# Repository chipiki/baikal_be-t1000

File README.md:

# baikal_be-t1000

## English

OpenHardware development board for Russian Baikal BE-T1000 MIPS Warrior P-class P5600 processor

Project status is "active schematic development". So, we haven't production PCB at this moment.

#### How to get this project:

First of all, get KiCAD EDA at http://kicad-pcb.org/download/

Install Git at https://git-scm.com/downloads if you don't have it allready.

Then do this commands in git-bash:
1) git clone https://github.com/chipiki/baikal_be-t1000.git
2) cd baikal_be-t1000
3) git submodule init
4) git submodule update
5) git submodule sync

Then launch KiCAD and open project file "baikal_be-t100.pro". 

## Русский

Открытый проект отладочной платы для отечественного процессора Байкал BE-T1000 MIPS32 Warrior P-class P5600.

Проект в стадии активной разработки схемы. Так, что, пока, готовой версии печатной платы нет на данный момент.

#### Как получить проект:

Для начала нужно скачать KiCAD на http://kicad-pcb.org/download/

Потом, необходимо установить Git отсюда https://git-scm.com/downloads , если он ещё не был установлен ранее.

Затем необходимо выполнить следующие команды в git-bash:
1) git clone https://github.com/chipiki/baikal_be-t1000.git
2) cd baikal_be-t1000
3) git submodule init
4) git submodule update
5) git submodule sync

Затем запустите KiCAD и откройте файл проекта "baikal_be-t100.pro".

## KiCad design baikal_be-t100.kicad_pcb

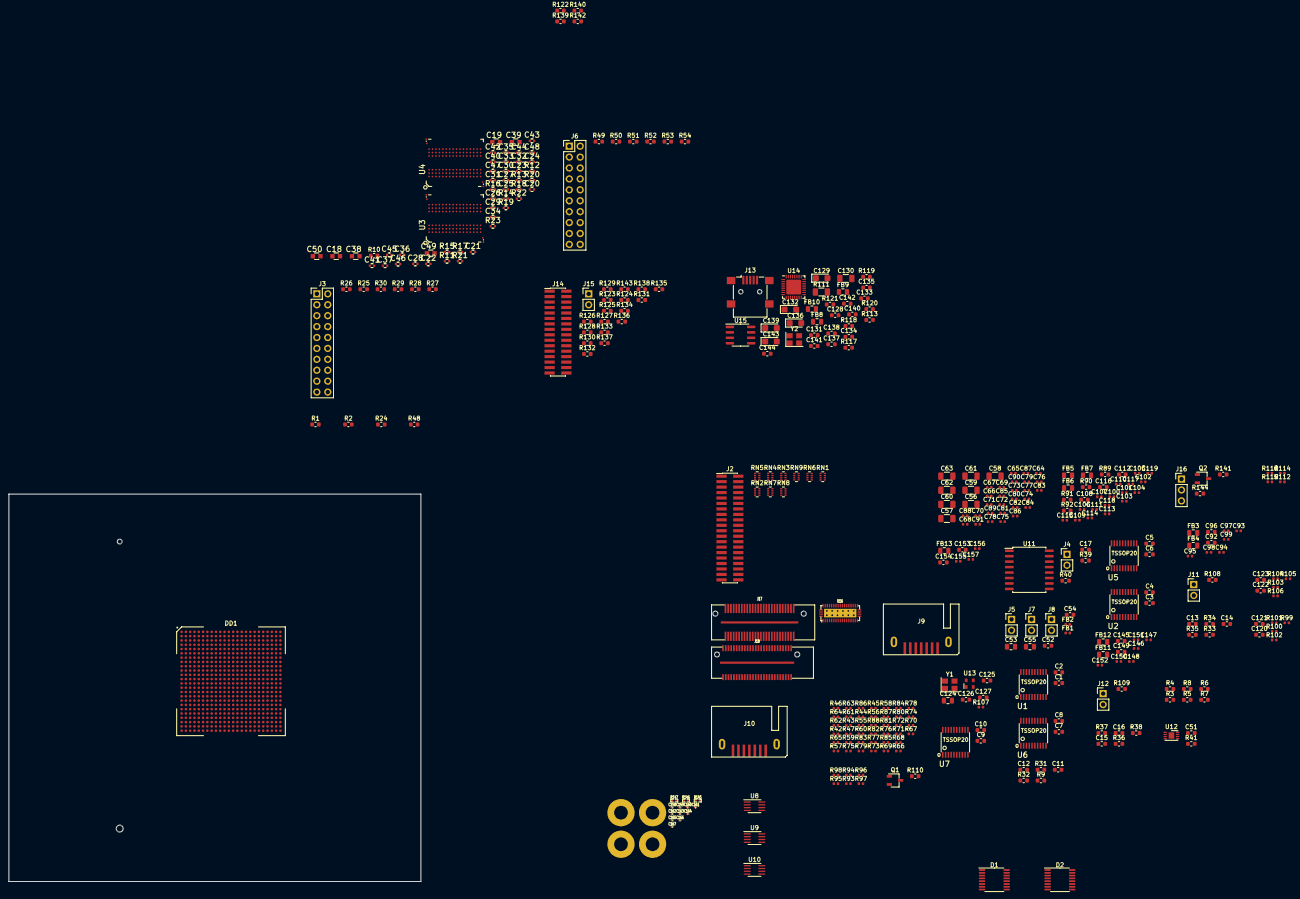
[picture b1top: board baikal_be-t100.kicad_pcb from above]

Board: 4 copper layers, 95.9 x 90.2 mm, 381 parts (1 on the bottom side), 402 nets, no tracks yet.

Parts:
C1, C2, C3, C4, C5, C6, C7, C8, C9, C10, C11, C12, C13, C14, C15, C16, C17, C51, C52, C54, C128, C131, C135, C137, C140, C142, C144: 0.1uF; C_0603_1608Metric
C18, C38, C39, C49, C50: 10uF/6.3V/20%; C_0603_5MIL_DWS
C19: 1uF/10V/10%; C_0603_5MIL_DWS
C20, C21, C22, C23, C24, C25, C26, C27, C28, C29, C30, C31, C32, C33, C34, C35, C36, C37, C40, C41, C42, C43, C44, C45, C46, C47, C48: 100nF/10V/10%; C_0402_5MIL_DWS
C53: 22uF; C_0805_2012Metric
C55, C124: 1uF; C_0805_2012Metric
C56, C57, C58, C59, C60, C61, C62, C63: 100uF; C_1206_3216Metric
C64, C65, C66, C67: 4.7uF; C_0402_1005Metric
C68, C69, C70, C71: 1uF; C_0402_1005Metric
C72, C73, C74, C75: 0.22uF; C_0402_1005Metric
C76, C77, C78, C79, C80, C81, C82, C83: 0.1uF; C_0402_1005Metric
C84, C85, C86, C87: 0.047uF; C_0402_1005Metric
C88, C89, C90, C91: 0.022uF; C_0402_1005Metric
C92, C96, C108, C112, C116, C145, C149, C153: 10uF/6.3V/0603; C_0603_1608Metric
C93, C97, C109, C113, C117, C146, C150: 4.7uF/10V/0402; C_0402_1005Metric
C94, C98, C110, C114, C118, C147, C151, C155: 0.1uF/10V/0402; C_0402_1005Metric
C95, C99, C111, C115, C119, C148, C152, C156, C157: 0.01uF/10V/0402; C_0402_1005Metric
C100, C101, C102, C103, C104, C105, C106, C107: 0.01uF; C_0402_1005Metric
C120, C121, C122, C123: 0.1uF/16V/X7R; C_0603_1608Metric
C125, C138, C141: 0.01uF; C_0603_1608Metric
C126, C127: 12pF; C_0603_1608Metric
C129, C132: 4.7uF/6.3V; CP_EIA-3216-18_Kemet-A
C130: 0.1uF; C_1206_3216Metric
C133, C134: 33pF; C_0603_1608Metric
C136, C139, C143: 10uF/6.3V; CP_EIA-3216-18_Kemet-A
C154: 1uF/10V/0402; C_0603_1608Metric
C158, C159, C163, C164, C165: 10nF; c_0201
C160, C161, C162, C166, C167: 100nF; c_0201
D1, D2: SN74AVC4T774PWR; TSSOP-16_4.4x5mm_P0.65mm
DD1: Baikal_BE-T1000; BGA-576_24x24_25.0x25.0mm
FB1, FB2: BLM15AX601SN1D; L_0402_1005Metric
FB3, FB4, FB5, FB6, FB7, FB11, FB12, FB13: MPZ2012S101AT000; L_0805_2012Metric
FB8, FB9, FB10: 500mA / 0.1DCR; L_0805_2012Metric
H1, H2, H3, H4: PCB_HOLE; PCIE104_HOLE
J1: 2-2013289-1; TE_2-2013289-1
J2: Conn_02x20_Odd_Even; PinHeader_2x20_P1.27mm_Vertical_SMD
J3, J6: Conn_02x10_Odd_Even; PinHeader_2x10_P2.54mm_Vertical
J4, J5, J7, J8, J11, J12, J15: Conn_01x02; PinHeader_1x02_P2.54mm_Vertical
J9, J10: 0473065005; SATA-MALE-7
J13: USB_OTG; USB_Mini-B_Lumberg_2486_01_Horizontal
J14: Conn_02x16_Odd_Even; PinHeader_2x16_P1.27mm_Vertical_SMD
J16: Conn_01x03; PinHeader_1x03_P2.54mm_Vertical
J17: OneBank Bottom; ASP-129646-22
J18: OneBank Top; ASP-129637-13
Q1, Q2: FDV305N; TSOT-23
R1, R10: 240; R_0603_1608Metric
R2: 200; R_0603_1608Metric
R3, R4, R5, R6, R7, R8, R9, R31, R32, R33, R34, R35, R36, R37, R38, R39, R40: 3K3; R_0603_1608Metric
R11, R12: 22R; R_0402_5MIL_DWS
R13, R14, R15, R16, R19: 2k/1%; R_0402_5MIL_DWS
R17, R22: 243R/1%; R_0402_5MIL_DWS
R18, R23: NA(243R/1%); R_0402_5MIL_DWS
R20: 100R/1%; R_0402_5MIL_DWS
R21: NA; R_0402_5MIL_DWS
R24, R48, R122, R123, R124, R125, R126, R127, R128, R129, R130, R131, R132, R133, R134, R135, R136, R137, R138, R139, R140: 33; R_0603_1608Metric
R25, R26, R27, R28, R29, R30, R49, R50, R51, R52, R53, R54: 47K; R_0603_1608Metric
R41: 0R; R_0603_1608Metric
R42, R43, R44, R45, R55, R56, R57, R58, R99, R100, R101, R102, R103, R104, R105, R106: 10K; R_0402_1005Metric
R46, R47, R59, R60: 4K7; R_0402_1005Metric
R61, R62, R63, R64, R65, R66, R67, R68, R69, R70, R71, R72, R73, R74, R75, R76, R77, R78, R79, R80, R81, R82, R83, R84: 33R; R_0402_1005Metric
R85, R86, R87, R88: 1K; R_0402_1005Metric
R89, R90, R91, R92, R118, R119: 0; R_0603_1608Metric
R93, R94, R95, R96, R97, R98, R107, R112, R114, R115, R116: 22R; R_0402_1005Metric
R108, R109, R120, R121, R142, R143: 4K7; R_0603_1608Metric
R110, R141, R144: 10K; R_0603_1608Metric
R111: 1M; R_1206_3216Metric
R113: 1M; R_0603_1608Metric
R117: 12K; R_0603_1608Metric
R145: DNP; r_0402
R146, R147: 10K; r_0402
RN1, RN2, RN3, RN4, RN5, RN6, RN7, RN8, RN9: YC124-JR-07100KL; R_Array_Concave_4x0402
U1, U2, U5, U6, U7: TXB0108PWR(TSSOP-20); TSSOP20_Pitch-0.65mm_6.6x4.5x1.2mm
U3, U4: K4B4G1646Q-HYK0(FBGA-96_256Mx16_DDR3-1600_11-11-1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; FBGA96(HYNIX_SAMSUNG_512MX16_DDR3)
U8, U9, U10: TCA9406DC; SSOP-8_2.95x2.8mm_P0.65mm
U11: DS3231M; SOIC-16W_7.5x10.3mm_P1.27mm
U12: AT24CS04-MAHM; DFN-8-1EP_3x2mm_P0.5mm_EP1.3x1.5mm
U13: ASDMB-xxxMHz; Oscillator_SMD_Abracon_ASDMB-4Pin_2.5x2.0mm
U14: USB3300-EZK; QFN-32-1EP_5x5mm_P0.5mm_EP3.45x3.45mm
U15: MIC2025-1YM; SOIC-8_3.9x4.9mm_P1.27mm
U16: CBTL04083A; HVQFN42
Y1: KX-7T 25MHz; Crystal_SMD_3225-4Pin_3.2x2.5mm
Y2: 24MHz; Crystal_SMD_3225-4Pin_3.2x2.5mm

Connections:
+0V95: C56.1, C57.1, C58.1, C59.1, C60.1, C61.1, C62.1, C63.1, C64.1, C65.1, C66.1, C67.1, C68.1, C69.1, C70.1, C71.1, C72.1, C73.1, C74.1, C75.1, C76.1, C77.1, C78.1, C79.1, C80.1, C81.1, C82.1, C83.1, C84.1, C85.1, C86.1, C87.1, C88.1, C89.1, C90.1, C91.1, DD1.A1, DD1.A8, DD1.A15, DD1.A22, DD1.AB4, DD1.AC1, DD1.AC19, DD1.AC20, DD1.E1, DD1.E16, DD1.G8, DD1.G9, DD1.G10, DD1.G11, DD1.G12, DD1.G13, DD1.G14, DD1.G15, DD1.G16, DD1.G22, DD1.J8, DD1.J9, DD1.J10, DD1.J11, DD1.J12, DD1.J13, DD1.J14, DD1.J15, DD1.J16, DD1.L8, DD1.L9, DD1.L10, DD1.L11, DD1.L12, DD1.L13, DD1.L14, DD1.L15, DD1.L16, DD1.M1, DD1.N8, DD1.N9, DD1.N10, DD1.N11, DD1.N12, DD1.N13, DD1.N14, DD1.N15, DD1.N16, DD1.R8, DD1.R9, DD1.R10, DD1.R11, DD1.R12, DD1.R13, DD1.R14, DD1.R15, DD1.R16, DD1.R22, DD1.U8, DD1.U9, DD1.U10, DD1.U11, DD1.U12, DD1.U13, DD1.U14, DD1.U15, DD1.U16, DD1.V3, DD1.W22, FB3.2, FB5.2, FB6.2, FB11.2
+1.5V: C18.1, C19.1, C20.1, C21.1, C22.1, C23.1, C24.2, C27.1, C30.1, C31.1, C32.1, C33.1, C34.1, C35.1, C36.1, C37.1, C38.1, C39.1, C41.1, C42.1, C43.1, C44.1, C45.1, C46.1, C47.1, C48.1, C49.1, C50.1, R13.2, R15.2, R19.2, U3.A1, U3.A8, U3.B2, U3.C1, U3.C9, U3.D2, U3.D9, U3.E9, U3.F1, U3.G7, U3.H2, U3.H9, U3.K2, U3.K8, U3.N1, U3.N9, U3.R1, U3.R9, U4.A1, U4.A8, U4.B2, U4.C1, U4.C9, U4.D2, U4.D9, U4.E9, U4.F1, U4.G7, U4.H2, U4.H9, U4.K2, U4.K8, U4.N1, U4.N9, U4.R1, U4.R9
+1V5: DD1.AB22, DD1.C22, DD1.D20, DD1.F19, DD1.H19, DD1.J24, DD1.K21, DD1.L19, DD1.L24, DD1.N18, DD1.N21, DD1.N24, DD1.R20, DD1.U20, DD1.U23, DD1.Y20, FB4.2, FB12.2
+1V8: C1.1, C3.1, C5.1, C7.1, C9.1, C11.1, C13.1, C15.1, C51.1, C120.1, C122.1, C124.1, C125.1, D1.16, D2.16, DD1.AB3, DD1.C4, DD1.C6, DD1.C7, DD1.C10, DD1.C12, DD1.F3, DD1.H3, DD1.L3, DD1.P3, DD1.T3, DD1.W3, DD1.Y17, FB1.1, FB2.1, FB7.2, FB13.2, J3.1, J6.1, J11.1, J12.1, J15.1, Q2.3, R3.1, R4.1, R5.1, R6.1, R7.1, R8.1, R25.1, R26.1, R27.1, R28.1, R29.1, R30.1, R41.1, R42.1, R43.1, R44.1, R45.1, R46.1, R47.1, R49.1, R50.1, R51.1, R52.1, R53.1, R54.1, R55.1, R56.1, R57.1, R58.1, R59.1, R60.1, R99.2, R100.2, R101.2, R103.2, R104.2, R105.2, R110.2, R142.1, U1.2, U1.10, U2.2, U2.10, U5.2, U5.10, U6.2, U6.10, U7.2, U7.10, U8.3, U9.3, U10.3, U12.8, U13.4
+1V35: J1.85, J1.86, J1.93, J1.94, J1.101, J1.102, J1.109, J1.110, J1.115, J1.116, J1.123, J1.124, J1.131, J1.132
+3.3V: C160.2, C161.2, C162.2, U16.5, U16.8, U16.13, U16.18, U16.20, U16.30, U16.40, U16.42
+3V3: C2.2, C4.2, C6.2, C8.2, C10.2, C12.2, C14.2, C16.2, C17.1, C121.1, C123.1, D1.15, D2.15, FB9.1, FB10.1, J1.199, J2.1, R9.1, R31.1, R32.1, R33.1, R34.1, R35.1, R36.1, R37.1, R38.1, R39.1, R40.1, RN1.1, RN1.2, RN1.3, RN1.4, RN2.1, RN2.2, RN2.3, RN2.4, RN3.1, RN3.2, RN3.3, RN3.4, RN4.1, RN4.2, RN4.3, RN4.4, RN5.1, RN5.2, RN5.3, RN5.4, RN6.1, RN6.2, RN6.3, RN6.4, RN7.1, RN7.2, RN7.3, RN7.4, RN8.1, RN8.2, RN8.3, RN8.4, RN9.1, RN9.2, RN9.3, RN9.4, U1.19, U2.19, U5.19, U6.19, U7.19, U8.6, U8.7, U9.6, U9.7, U10.6, U10.7, U11.2
+5V: C135.1, J17.53, J18.53, R145.2, U15.7
/CPU/CPU_1G_Eth/ZZZZZ: R65.2, R67.2, R69.2, R71.2, R73.2, R75.2, R77.2, R79.2, R81.2, R83.2
/CPU/CPU_BOOT/BOOTCFG_0: DD1.AC3, J11.2, R108.1
/CPU/CPU_BOOT/BOOTCFG_1: DD1.AC4, J12.2, R109.1
/CPU/CPU_BOOT/CLK_25M_IN: C127.1, DD1.R2, Y1.3
/CPU/CPU_BOOT/CLK_25M_OUT: C126.1, DD1.R1, Y1.1
/CPU/CPU_BOOT/RESET: DD1.T1, Q1.3, R110.1
/CPU/CPU_DEBUG/CPU_EJTAG/EJTAG20_Conn/DBGRQ: DD1.A14, J3.17, R30.2
/CPU/CPU_DEBUG/CPU_EJTAG/EJTAG20_Conn/TCK: DD1.A13, J3.9, R28.2
/CPU/CPU_DEBUG/CPU_EJTAG/EJTAG20_Conn/TDI: DD1.C14, J3.5, R26.2
/CPU/CPU_DEBUG/CPU_EJTAG/EJTAG20_Conn/TDO: J3.13, R24.2, R29.2
/CPU/CPU_DEBUG/CPU_EJTAG/EJTAG20_Conn/TMS: DD1.B14, J3.7, R27.2
/CPU/CPU_DEBUG/CPU_EJTAG/EJTAG20_Conn/nTRST: DD1.B13, J3.3, R25.2
/CPU/CPU_DEBUG/CPU_JTAG/JTAG20_Conn/DBGRQ: J6.17, R54.2
/CPU/CPU_DEBUG/CPU_JTAG/JTAG20_Conn/TCK: DD1.AA1, J6.9, R52.2
/CPU/CPU_DEBUG/CPU_JTAG/JTAG20_Conn/TDI: DD1.AB2, J6.5, R50.2
/CPU/CPU_DEBUG/CPU_JTAG/JTAG20_Conn/TDO: DD1.AB1, J6.13, R53.2
/CPU/CPU_DEBUG/CPU_JTAG/JTAG20_Conn/TMS: DD1.AA2, J6.7, R51.2
/CPU/CPU_DEBUG/CPU_JTAG/JTAG20_Conn/nTRST: J6.3, R48.2, R49.2
/CPU/CPU_DEBUG/CPU_TRACE/TR_CLK: J14.15, R122.2
/CPU/CPU_DEBUG/CPU_TRACE/TR_DATA0: J14.2, R123.2
/CPU/CPU_DEBUG/CPU_TRACE/TR_DATA1: J14.4, R124.2
/CPU/CPU_DEBUG/CPU_TRACE/TR_DATA2: J14.6, R125.2
/CPU/CPU_DEBUG/CPU_TRACE/TR_DATA3: J14.8, R126.2
/CPU/CPU_DEBUG/CPU_TRACE/TR_DATA4: J14.10, R127.2
/CPU/CPU_DEBUG/CPU_TRACE/TR_DATA5: J14.12, R128.2
/CPU/CPU_DEBUG/CPU_TRACE/TR_DATA6: J14.14, R129.2
/CPU/CPU_DEBUG/CPU_TRACE/TR_DATA7: J14.16, R130.2
/CPU/CPU_DEBUG/CPU_TRACE/TR_DATA8: J14.18, R131.2
/CPU/CPU_DEBUG/CPU_TRACE/TR_DATA9: J14.20, R132.2
/CPU/CPU_DEBUG/CPU_TRACE/TR_DATA10: J14.22, R133.2
/CPU/CPU_DEBUG/CPU_TRACE/TR_DATA11: J14.24, R134.2
/CPU/CPU_DEBUG/CPU_TRACE/TR_DATA12: J14.26, R135.2
/CPU/CPU_DEBUG/CPU_TRACE/TR_DATA13: J14.28, R136.2
/CPU/CPU_DEBUG/CPU_TRACE/TR_DATA14: J14.30, R137.2
/CPU/CPU_DEBUG/CPU_TRACE/TR_DATA15: J14.32, R138.2
/CPU/CPU_DEBUG/CPU_TRACE/TR_DM: J14.17, R139.2
/CPU/CPU_DEBUG/CPU_TRACE/TR_PROBE_N: DD1.E13, J14.19, R142.2
/CPU/CPU_DEBUG/CPU_TRACE/TR_TEST: DD1.F14, J14.9, J15.2, R143.2
/CPU/CPU_DEBUG/CPU_TRACE/TR_TRIGIN: DD1.D13, J14.21
/CPU/CPU_DEBUG/CPU_TRACE/TR_TRIGOUT: J14.23, R140.2
/CPU/CPU_DEBUG/CPU_TRACE/TSTSEL_3: DD1.U3, J14.29, Q2.2, R144.2
/CPU/CPU_GPIO/GPIO3_0: DD1.W7, U7.1
/CPU/CPU_GPIO/GPIO3_0_3V3: J2.30, RN9.8, U7.20
/CPU/CPU_GPIO/GPIO3_1: DD1.W6, U7.3
/CPU/CPU_GPIO/GPIO3_1_3V3: J2.32, RN9.7, U7.18
/CPU/CPU_GPIO/GPIO3_2: DD1.W5, U7.4
/CPU/CPU_GPIO/GPIO3_2_3V3: J2.34, RN9.6, U7.17
/CPU/CPU_GPIO/GPIO_0: DD1.F9, U1.1
/CPU/CPU_GPIO/GPIO_0_3V3: J2.3, RN1.8, U1.20
/CPU/CPU_GPIO/GPIO_1: DD1.F8, U1.3
/CPU/CPU_GPIO/GPIO_1_3V3: J2.5, RN1.7, U1.18
/CPU/CPU_GPIO/GPIO_2: DD1.F7, U1.4
/CPU/CPU_GPIO/GPIO_2_3V3: J2.7, RN1.6, U1.17
/CPU/CPU_GPIO/GPIO_3: DD1.E6, U1.5
/CPU/CPU_GPIO/GPIO_3_3V3: J2.9, RN1.5, U1.16
/CPU/CPU_GPIO/GPIO_4: DD1.E5, U1.6
/CPU/CPU_GPIO/GPIO_4_3V3: J2.11, RN2.8, U1.15
/CPU/CPU_GPIO/GPIO_5: DD1.E4, U1.7
/CPU/CPU_GPIO/GPIO_5_3V3: J2.13, RN2.7, U1.14
/CPU/CPU_GPIO/GPIO_6: DD1.D5, U1.8
/CPU/CPU_GPIO/GPIO_6_3V3: J2.15, RN2.6, U1.13
/CPU/CPU_GPIO/GPIO_7: DD1.D3, U1.9
/CPU/CPU_GPIO/GPIO_7_3V3: J2.17, RN2.5, U1.12
/CPU/CPU_GPIO/GPIO_8: DD1.A5, U2.1
/CPU/CPU_GPIO/GPIO_8_3V3: J2.19, RN3.8, U2.20
/CPU/CPU_GPIO/GPIO_9: DD1.D2, U2.3
/CPU/CPU_GPIO/GPIO_9_3V3: J2.21, RN3.7, U2.18
/CPU/CPU_GPIO/GPIO_10: DD1.D1, U2.4
/CPU/CPU_GPIO/GPIO_10_3V3: J2.23, RN3.6, U2.17
/CPU/CPU_GPIO/GPIO_11: DD1.C5, U2.5
/CPU/CPU_GPIO/GPIO_11_3V3: J2.25, RN3.5, U2.16
/CPU/CPU_GPIO/GPIO_12: DD1.C3, U2.6
/CPU/CPU_GPIO/GPIO_12_3V3: J2.27, RN4.8, U2.15
/CPU/CPU_GPIO/GPIO_13: DD1.C2, U2.7
/CPU/CPU_GPIO/GPIO_13_3V3: J2.29, RN4.7, U2.14
/CPU/CPU_GPIO/GPIO_14: DD1.B5, U2.8
/CPU/CPU_GPIO/GPIO_14_3V3: J2.31, RN4.6, U2.13
/CPU/CPU_GPIO/GPIO_15: DD1.B3, U2.9
/CPU/CPU_GPIO/GPIO_15_3V3: J2.33, RN4.5, U2.12
/CPU/CPU_GPIO/GPIO_16: DD1.E3, U5.1
/CPU/CPU_GPIO/GPIO_16_3V3: J2.35, RN5.8, U5.20
/CPU/CPU_GPIO/GPIO_17: DD1.B2, U5.3
/CPU/CPU_GPIO/GPIO_17_3V3: J2.37, RN5.7, U5.18
/CPU/CPU_GPIO/GPIO_18: DD1.C1, U5.4
/CPU/CPU_GPIO/GPIO_18_3V3: J2.39, RN5.6, U5.17
/CPU/CPU_GPIO/GPIO_19: DD1.A2, U5.5
/CPU/CPU_GPIO/GPIO_19_3V3: J2.4, RN5.5, U5.16
/CPU/CPU_GPIO/GPIO_20: DD1.A4, U5.6
/CPU/CPU_GPIO/GPIO_20_3V3: J2.6, RN6.8, U5.15
/CPU/CPU_GPIO/GPIO_21: DD1.B4, U5.7
/CPU/CPU_GPIO/GPIO_21_3V3: J2.8, RN6.7, U5.14
/CPU/CPU_GPIO/GPIO_22: DD1.A3, U5.8
/CPU/CPU_GPIO/GPIO_22_3V3: J2.10, RN6.6, U5.13
/CPU/CPU_GPIO/GPIO_23: DD1.B6, U5.9
/CPU/CPU_GPIO/GPIO_23_3V3: J2.12, RN6.5, U5.12
/CPU/CPU_GPIO/GPIO_24: DD1.A6, U6.1
/CPU/CPU_GPIO/GPIO_24_3V3: J2.14, RN7.8, U6.20
/CPU/CPU_GPIO/GPIO_25: DD1.F10, U6.3
/CPU/CPU_GPIO/GPIO_25_3V3: J2.16, RN7.7, U6.18
/CPU/CPU_GPIO/GPIO_26: DD1.E8, U6.4
/CPU/CPU_GPIO/GPIO_26_3V3: J2.18, RN7.6, U6.17
/CPU/CPU_GPIO/GPIO_27: DD1.E7, U6.5
/CPU/CPU_GPIO/GPIO_27_3V3: J2.20, RN7.5, U6.16
/CPU/CPU_GPIO/GPIO_28: DD1.B7, U6.6
/CPU/CPU_GPIO/GPIO_28_3V3: J2.22, RN8.8, U6.15
/CPU/CPU_GPIO/GPIO_29: DD1.A7, U6.7
/CPU/CPU_GPIO/GPIO_29_3V3: J2.24, RN8.7, U6.14
/CPU/CPU_GPIO/GPIO_30: DD1.E9, U6.8
/CPU/CPU_GPIO/GPIO_30_3V3: J2.26, RN8.6, U6.13
/CPU/CPU_GPIO/GPIO_31: DD1.D8, U6.9
/CPU/CPU_GPIO/GPIO_31_3V3: J2.28, RN8.5, U6.12
/CPU/CPU_I2C/I2C0_SCL: DD1.AD5, R3.2, U8.5
/CPU/CPU_I2C/I2C0_SCL_3V3: R9.2, U8.8
/CPU/CPU_I2C/I2C0_SDA: DD1.AD4, R4.2, U8.4
/CPU/CPU_I2C/I2C0_SDA_3V3: R31.2, U8.1
/CPU/CPU_I2C/I2C1_SCL: DD1.K7, R5.2, U9.5
/CPU/CPU_I2C/I2C1_SCL_3V3: R33.2, U9.8
/CPU/CPU_I2C/I2C1_SDA: DD1.K6, R6.2, U9.4
/CPU/CPU_I2C/I2C1_SDA_3V3: R34.2, U9.1
/CPU/CPU_I2C/I2C2_SCL: DD1.J1, R7.2, U10.5, U12.6
/CPU/CPU_I2C/I2C2_SCL_3V3: R36.2, U10.8, U11.16
/CPU/CPU_I2C/I2C2_SDA: DD1.K1, R8.2, U10.4, U12.5
/CPU/CPU_I2C/I2C2_SDA_3V3: R37.2, U10.1, U11.15
/CPU/CPU_POWER/GPVT: DD1.G17, J7.1
/CPU/CPU_POWER/VPVT: DD1.F17, J5.2
/CPU/CPU_POWER/VQPVS: DD1.V7, J8.2
/CPU/CPU_SATA/SATA1_CON_RX_N: C106.1, J9.5
/CPU/CPU_SATA/SATA1_CON_RX_P: C104.1, J9.6
/CPU/CPU_SATA/SATA1_CON_TX_N: C102.1, J9.3
/CPU/CPU_SATA/SATA1_CON_TX_P: C100.1, J9.2
/CPU/CPU_SATA/SATA2_CON_RX_N: C107.1, J10.5
/CPU/CPU_SATA/SATA2_CON_RX_P: C105.1, J10.6
/CPU/CPU_SATA/SATA2_CON_TX_N: C103.1, J10.3
/CPU/CPU_SATA/SATA2_CON_TX_P: C101.1, J10.2
/CPU/CPU_SATA/SATA_RXM0_N: C106.2, DD1.B19
/CPU/CPU_SATA/SATA_RXM1_N: C107.2, DD1.B17
/CPU/CPU_SATA/SATA_RXP0_P: C104.2, DD1.A19
/CPU/CPU_SATA/SATA_RXP1_P: C105.2, DD1.A17
/CPU/CPU_SATA/SATA_TXM0_N: C102.2, DD1.B18
/CPU/CPU_SATA/SATA_TXM1_N: C103.2, DD1.B16
/CPU/CPU_SATA/SATA_TXP0_P: C100.2, DD1.A18
/CPU/CPU_SATA/SATA_TXP1_P: C101.2, DD1.A16
/CPU/CPU_SPI/SPI1_CLK: D1.5, R95.2
/CPU/CPU_SPI/SPI1_MISO: D1.4, DD1.F6
/CPU/CPU_SPI/SPI1_MOSI: D1.3, R96.2
/CPU/CPU_SPI/SPI2_CLK: D2.5, R97.2
/CPU/CPU_SPI/SPI2_MISO: D2.4, DD1.H5
/CPU/CPU_SPI/SPI2_MOSI: D2.3, R98.2
/CPU/CPU_ULPI/EXTBUS_FLG: DD1.K5, U14.10, U15.2
/CPU/CPU_ULPI/ULPI_CLK: R112.1, U14.14
/CPU/CPU_ULPI/ULPI_DATA0: DD1.L1, U14.24
/CPU/CPU_ULPI/ULPI_DATA1: DD1.L2, U14.23
/CPU/CPU_ULPI/ULPI_DATA2: DD1.L5, U14.22
/CPU/CPU_ULPI/ULPI_DATA3: DD1.M5, U14.21
/CPU/CPU_ULPI/ULPI_DATA4: DD1.M6, U14.20
/CPU/CPU_ULPI/ULPI_DATA5: DD1.M7, U14.19
/CPU/CPU_ULPI/ULPI_DATA6: DD1.M3, U14.18
/CPU/CPU_ULPI/ULPI_DATA7: DD1.M4, U14.17
/CPU/CPU_ULPI/ULPI_DIR: R114.1, U14.12
/CPU/CPU_ULPI/ULPI_NXT: R115.1, U14.11
/CPU/CPU_ULPI/ULPI_RESET: R120.2, U14.9
/CPU/CPU_ULPI/ULPI_STP: R116.1, U14.13
/CPU/CPU_ULPI/USBD_ID: J13.4, U14.5
/CPU/CPU_ULPI/USBD_N: J13.2, U14.8
/CPU/CPU_ULPI/USBD_P: J13.3, U14.7
/CPU/CPU_ULPI/USB_VBUS: C143.1, C144.1, DD1.L7, J13.1, U14.4, U15.6, U15.8
/CPU/CPU_ULPI/USB_VDD3.3V: C136.1, C137.1, C138.1, C142.1, R118.1, U14.16, U14.25, U14.31
/CPU/CPU_ULPI/USB_VDDA3.3V: C139.1, C140.1, C141.1, R119.1, U14.6, U14.30
/CPU/CPU_ULPI/VBUS_EN: U14.3, U15.1
/CPU/DDR3_chip/S0SA0: DD1.K19, U3.N3, U4.N3
/CPU/DDR3_chip/S0SA1: DD1.K24, U3.P7, U4.P7
/CPU/DDR3_chip/S0SA2: DD1.K22, U3.P3, U4.P3
/CPU/DDR3_chip/S0SA3: DD1.M22, U3.N2, U4.N2
/CPU/DDR3_chip/S0SA4: DD1.M18, U3.P8, U4.P8
/CPU/DDR3_chip/S0SA5: DD1.P21, U3.P2, U4.P2
/CPU/DDR3_chip/S0SA6: DD1.N19, U3.R8, U4.R8
/CPU/DDR3_chip/S0SA7: DD1.P19, U3.R2, U4.R2
/CPU/DDR3_chip/S0SA8: DD1.P20, U3.T8, U4.T8
/CPU/DDR3_chip/S0SA9: DD1.M21, U3.R3, U4.R3
/CPU/DDR3_chip/S0SA10: DD1.H22, U3.L7, U4.L7
/CPU/DDR3_chip/S0SA11: DD1.M20, U3.R7, U4.R7
/CPU/DDR3_chip/S0SA12: DD1.K18, U3.N7, U4.N7
/CPU/DDR3_chip/S0SA13: DD1.M19, U3.T3, U4.T3
/CPU/DDR3_chip/S0SA14: DD1.L20, U3.T7, U4.T7
/CPU/DDR3_chip/S0SA15: DD1.J21, U3.M7, U4.M7
/CPU/DDR3_chip/S0SBA0: DD1.N22, U3.M2, U4.M2
/CPU/DDR3_chip/S0SBA1: DD1.J19, U3.N8, U4.N8
/CPU/DDR3_chip/S0SBA2: DD1.G20, U3.M3, U4.M3
/CPU/DDR3_chip/S0SCAS: DD1.J22, U3.K3, U4.K3
/CPU/DDR3_chip/S0SCKE0: DD1.K23, U3.K9, U4.K9
/CPU/DDR3_chip/S0SCKE1: DD1.H20, U3.J9, U4.J9
/CPU/DDR3_chip/S0SCK_N: R12.1, R20.1, U3.K7, U4.K7
/CPU/DDR3_chip/S0SCK_P: R11.1, R20.2, U3.J7, U4.J7
/CPU/DDR3_chip/S0SCS0: DD1.H23, U3.L2, U4.L2
/CPU/DDR3_chip/S0SCS1: DD1.J20, U3.L1, U4.L1
/CPU/DDR3_chip/S0SDQ0: DD1.AA19, U3.F7
/CPU/DDR3_chip/S0SDQ1: DD1.AA22, U3.G2
/CPU/DDR3_chip/S0SDQ2: DD1.AB23, U3.F2
/CPU/DDR3_chip/S0SDQ3: DD1.AB24, U3.H7
/CPU/DDR3_chip/S0SDQ4: DD1.AD22, U3.E3
/CPU/DDR3_chip/S0SDQ5: DD1.AA20, U3.H3
/CPU/DDR3_chip/S0SDQ6: DD1.AD21, U3.H8
/CPU/DDR3_chip/S0SDQ7: DD1.AA21, U3.F8
/CPU/DDR3_chip/S0SDQ8: DD1.V22, U3.A7
/CPU/DDR3_chip/S0SDQ9: DD1.V23, U3.C8
/CPU/DDR3_chip/S0SDQ10: DD1.V24, U3.B8
/CPU/DDR3_chip/S0SDQ11: DD1.Y22, U3.D7
/CPU/DDR3_chip/S0SDQ12: DD1.Y21, U3.A3
/CPU/DDR3_chip/S0SDQ13: DD1.AA24, U3.C2
/CPU/DDR3_chip/S0SDQ14: DD1.AA23, U3.C3
/CPU/DDR3_chip/S0SDQ15: DD1.V21, U3.A2
/CPU/DDR3_chip/S0SDQ16: DD1.V20, U4.F7
/CPU/DDR3_chip/S0SDQ17: DD1.P23, U4.H8
/CPU/DDR3_chip/S0SDQ18: DD1.P24, U4.H7
/CPU/DDR3_chip/S0SDQ19: DD1.R21, U4.F8
/CPU/DDR3_chip/S0SDQ20: DD1.T21, U4.H3
/CPU/DDR3_chip/S0SDQ21: DD1.U24, U4.F2
/CPU/DDR3_chip/S0SDQ22: DD1.U21, U4.E3
/CPU/DDR3_chip/S0SDQ23: DD1.T20, U4.G2
/CPU/DDR3_chip/S0SDQ24: DD1.G21, U4.A7
/CPU/DDR3_chip/S0SDQ25: DD1.E21, U4.C8
/CPU/DDR3_chip/S0SDQ26: DD1.E22, U4.D7
/CPU/DDR3_chip/S0SDQ27: DD1.E20, U4.B8
/CPU/DDR3_chip/S0SDQ28: DD1.F21, U4.A3
/CPU/DDR3_chip/S0SDQ29: DD1.E24, U4.C3
/CPU/DDR3_chip/S0SDQ30: DD1.E23, U4.A2
/CPU/DDR3_chip/S0SDQ31: DD1.F20, U4.C2
/CPU/DDR3_chip/S0SDQM0: DD1.AC22, U3.E7
/CPU/DDR3_chip/S0SDQM1: DD1.W21, U3.D3
/CPU/DDR3_chip/S0SDQM2: DD1.T22, U4.E7
/CPU/DDR3_chip/S0SDQM3: DD1.F22, U4.D3
/CPU/DDR3_chip/S0SDQS0_N: DD1.AC24, U3.G3
/CPU/DDR3_chip/S0SDQS0_P: DD1.AC23, U3.F3
/CPU/DDR3_chip/S0SDQS1_N: DD1.Y24, U3.B7
/CPU/DDR3_chip/S0SDQS1_P: DD1.Y23, U3.C7
/CPU/DDR3_chip/S0SDQS2_N: DD1.T24, U4.G3
/CPU/DDR3_chip/S0SDQS2_P: DD1.T23, U4.F3
/CPU/DDR3_chip/S0SDQS3_N: DD1.F24, U4.B7
/CPU/DDR3_chip/S0SDQS3_P: DD1.F23, U4.C7
/CPU/DDR3_chip/S0SODT0: DD1.H24, U3.K1, U4.K1
/CPU/DDR3_chip/S0SODT1: DD1.P22, U3.J1, U4.J1
/CPU/DDR3_chip/S0SRAS: DD1.H21, U3.J3, U4.J3
/CPU/DDR3_chip/S0SRST: DD1.T19, R19.1, U3.T2, U4.T2
/CPU/DDR3_chip/S0SVREF: C24.1, C25.2, C26.2, DD1.E18, DD1.H17, DD1.J18, DD1.M17, DD1.R18, DD1.U18, DD1.W19, R13.1, R14.2, R21.2
/CPU/DDR3_chip/S0SWE: DD1.G19, U3.L3, U4.L3
/CPU/DDR3_chip/VREF0_DDR3: C27.2, C28.1, C29.1, C40.1, R15.1, R16.2, R21.1, U3.H1, U3.M8, U4.H1, U4.M8
/CPU/OneBank/BTM_0CK_N: J17.38, U16.28
/CPU/OneBank/BTM_0CK_P: J17.36, U16.29
/CPU/OneBank/BTM_0RX_N: J17.26, U16.35
/CPU/OneBank/BTM_0RX_P: J17.24, U16.36
/CPU/OneBank/BTM_0TX_N: J17.14, U16.37
/CPU/OneBank/BTM_0TX_P: J17.12, U16.38
/CPU/OneBank/BTM_1CK_N: J17.37, J18.38
/CPU/OneBank/BTM_1CK_P: J17.35, J18.36
/CPU/OneBank/BTM_1RX_N: J17.25, J18.26
/CPU/OneBank/BTM_1RX_P: J17.23, J18.24
/CPU/OneBank/BTM_1TX_N: J17.13, J18.14
/CPU/OneBank/BTM_1TX_P: J17.11, J18.12
/CPU/OneBank/BTM_2CK_N: J17.43, J18.37
/CPU/OneBank/BTM_2CK_P: J17.41, J18.35
/CPU/OneBank/BTM_2RX_N: J17.31, J18.25
/CPU/OneBank/BTM_2RX_P: J17.29, J18.23
/CPU/OneBank/BTM_2TX_N: J17.19, J18.13
/CPU/OneBank/BTM_2TX_P: J17.17, J18.11
/CPU/OneBank/BTM_3CK_N: J17.44, J18.43
/CPU/OneBank/BTM_3CK_P: J17.42, J18.41
/CPU/OneBank/BTM_3RX_N: J17.32, J18.31
/CPU/OneBank/BTM_3RX_P: J17.30, J18.29
/CPU/OneBank/BTM_3TX_N: J17.20, J18.19
/CPU/OneBank/BTM_3TX_P: J17.18, J18.17
/CPU/OneBank/MGTXTX0_B_N: C167.2, U16.7
/CPU/OneBank/MGTXTX0_B_P: C166.2, U16.6
/CPU/OneBank/OB_3V3: J17.3, J17.4, J18.3, J18.4
/CPU/OneBank/OB_ALERT: J17.51, J18.51
/CPU/OneBank/OB_DIR: C163.1, J17.45, J18.45, R146.2
/CPU/OneBank/OB_PE_RST: J17.2, J18.2
/CPU/OneBank/OB_PG: C164.1, J17.46, J18.46
/CPU/OneBank/OB_PSON: C165.1, J17.52, J18.52
/CPU/OneBank/OB_USB0_N: J17.8, J18.8
/CPU/OneBank/OB_USB0_P: J17.6, J18.6
/CPU/OneBank/OB_USB1_N: J17.7, J18.7
/CPU/OneBank/OB_USB1_P: J17.5, J18.5
/CPU/OneBank/OB_USB_OC: J17.1, J18.1
/CPU/OneBank/SMBUS_SCL: J17.49, J18.49
/CPU/OneBank/SMBUS_SDA: J17.47, J18.47
/CPU/OneBank/TOP_3CK_N: J18.44, U16.24
/CPU/OneBank/TOP_3CK_P: J18.42, U16.25
/CPU/OneBank/TOP_3RX_N: J18.32, U16.31
/CPU/OneBank/TOP_3RX_P: J18.30, U16.32
/CPU/OneBank/TOP_3TX_N: J18.20, U16.33
/CPU/OneBank/TOP_3TX_P: J18.18, U16.34
GND: C158.2, C159.2, C160.1, C161.1, C162.1, C163.2, C164.2, C165.2, J17.9, J17.10, J17.15, J17.16, J17.21, J17.22, J17.27, J17.28, J17.33, J17.34, J18.9, J18.10, J18.15, J18.16, J18.21, J18.22, J18.27, J18.28, J18.33, J18.34, R147.2, U16.1, U16.4, U16.10, U16.14, U16.17, U16.19, U16.21, U16.39, U16.41, U16.43
GNDD: C1.2, C2.1, C3.2, C4.1, C5.2, C6.1, C7.2, C8.1, C9.2, C10.1, C11.2, C12.1, C13.2, C14.1, C15.2, C16.1, C17.2, C18.2, C19.2, C20.2, C21.2, C22.2, C23.2, C25.1, C26.1, C28.2, C29.2, C30.2, C31.2, C32.2, C33.2, C34.2, C35.2, C36.2, C37.2, C38.2, C39.2, C40.2, C41.2, C42.2, C43.2, C44.2, C45.2, C46.2, C47.2, C48.2, C49.2, C50.2, C51.2, C54.2, C55.2, C56.2, C57.2, C58.2, C59.2, C60.2, C61.2, C62.2, C63.2, C64.2, C65.2, C66.2, C67.2, C68.2, C69.2, C70.2, C71.2, C72.2, C73.2, C74.2, C75.2, C76.2, C77.2, C78.2, C79.2, C80.2, C81.2, C82.2, C83.2, C84.2, C85.2, C86.2, C87.2, C88.2, C89.2, C90.2, C91.2, C92.2, C93.2, C94.2, C95.2, C96.2, C97.2, C98.2, C99.2, C108.2, C109.2, C110.2, C111.2, C112.2, C113.2, C114.2, C115.2, C116.2, C117.2, C118.2, C119.2, C120.2, C121.2, C122.2, C123.2, C124.2, C125.2, C126.2, C127.2, C128.2, C129.2, C130.2, C131.2, C132.2, C133.2, C134.2, C135.2, C136.2, C137.2, C138.2, C139.2, C140.2, C141.2, C143.2, C144.2, C145.2, C146.2, C147.2, C148.2, C149.2, C150.2, C151.2, C152.2, C153.2, C154.2, C155.2, C156.2, C157.2, D1.9, D1.10, D2.9, D2.10, DD1.A23, DD1.AA3, DD1.AA4, DD1.AB5, DD1.AB7, DD1.AB9, DD1.AB12, DD1.AB14, DD1.AB15, DD1.AB17, DD1.AB19, DD1.AB20, DD1.AB21, DD1.AD2, DD1.AD23, DD1.B1, DD1.B8, DD1.B15, DD1.C16, DD1.C21, DD1.D4, DD1.D6, DD1.D7, DD1.D10, DD1.D12, DD1.E2, DD1.E17, DD1.E19, DD1.F4, DD1.F18, DD1.G23, DD1.H4, DD1.H8, DD1.H9, DD1.H10, DD1.H11, DD1.H12, DD1.H13, DD1.H14, DD1.H15, DD1.H16, DD1.H18, DD1.J23, DD1.K8, DD1.K9, DD1.K10, DD1.K11, DD1.K12, DD1.K13, DD1.K14, DD1.K15, DD1.K16, DD1.K20, DD1.L4, DD1.L18, DD1.L23, DD1.M2, DD1.M8, DD1.M9, DD1.M10, DD1.M11, DD1.M12, DD1.M13, DD1.M14, DD1.M15, DD1.M16, DD1.N17, DD1.N20, DD1.N23, DD1.P4, DD1.P8, DD1.P9, DD1.P10, DD1.P11, DD1.P12, DD1.P13, DD1.P14, DD1.P15, DD1.P16, DD1.R19, DD1.R23, DD1.T4, DD1.T8, DD1.T9, DD1.T10, DD1.T11, DD1.T12, DD1.T13, DD1.T14, DD1.T15, DD1.T16, DD1.U2, DD1.U19, DD1.U22, DD1.V8, DD1.V9, DD1.V10, DD1.V11, DD1.V12, DD1.V13, DD1.V14, DD1.V15, DD1.V16, DD1.W4, DD1.W9, DD1.W14, DD1.W17, DD1.W20, DD1.W23, DD1.Y11, DD1.Y19, FB8.1, J1.2, J1.3, J1.8, J1.9, J1.14, J1.17, J1.20, J1.23, J1.26, J1.29, J1.32, J1.35, J1.38, J1.41, J1.46, J1.47, J1.52, J1.53, J1.58, J1.61, J1.64, J1.67, J1.70, J1.73, J1.78, J1.79, J1.137, J1.138, J1.143, J1.146, J1.149, J1.152, J1.155, J1.158, J1.163, J1.164, J1.169, J1.170, J1.175, J1.178, J1.181, J1.184, J1.187, J1.190, J1.195, J1.196, J1.197, J1.201, J2.2, J3.4, J3.6, J3.8, J3.10, J3.11, J3.12, J3.14, J3.16, J3.18, J3.20, J4.2, J6.4, J6.6, J6.8, J6.10, J6.11, J6.12, J6.14, J6.16, J6.18, J6.20, J9.1, J9.4, J9.7, J10.1, J10.4, J10.7, J14.31, Q1.2, R1.1, R2.1, R10.1, R14.1, R16.1, R17.2, R18.2, R22.2, R23.2, R32.2, R35.2, R38.2, R85.1, R86.1, R87.1, R88.1, R89.1, R90.1, R91.1, R92.1, R102.2, R106.2, R108.2, R109.2, R111.1, R117.1, R121.1, R141.1, R143.1, R144.1, U1.11, U2.11, U3.A9, U3.B1, U3.B3, U3.B9, U3.D1, U3.D8, U3.E1, U3.E2, U3.E8, U3.F9, U3.G1, U3.G8, U3.G9, U3.J2, U3.J8, U3.M1, U3.M9, U3.P1, U3.P9, U3.T1, U3.T9, U4.A9, U4.B1, U4.B3, U4.B9, U4.D1, U4.D8, U4.E1, U4.E2, U4.E8, U4.F9, U4.G1, U4.G8, U4.G9, U4.J2, U4.J8, U4.M1, U4.M9, U4.P1, U4.P9, U4.T1, U4.T9, U5.11, U6.11, U7.11, U8.2, U9.2, U10.2, U11.5, U11.6, U11.7, U11.8, U11.9, U11.10, U11.11, U11.12, U11.13, U12.2, U12.4, U12.7, U13.2, U14.1, U14.2, U14.33, U15.3, Y1.2, Y1.4, Y2.2, Y2.4
unnamed: J4.1, U11.14
unnamed: C52.1, C53.1, FB1.2, J5.1
unnamed: C52.2, C53.2, J7.2
unnamed: C54.1, C55.1, FB2.2, J8.1
unnamed: C92.1, C93.1, C94.1, C95.1, DD1.AA14, DD1.AB13, DD1.AB16, FB3.1
unnamed: C96.1, C97.1, C98.1, C99.1, DD1.Y14, FB4.1
unnamed: C108.1, C109.1, C110.1, C111.1, DD1.C17, FB5.1
unnamed: C112.1, C113.1, C114.1, C115.1, DD1.C18, FB6.1
unnamed: C116.1, C117.1, C118.1, C119.1, DD1.C20, FB7.1
unnamed: C128.1, C129.1, U14.15, U14.26
unnamed: C130.1, J13.6, R111.2
unnamed: C131.1, C132.1, U14.29
unnamed: C133.1, R113.2, U14.27, Y2.1
unnamed: C134.1, R113.1, U14.28, Y2.3
unnamed: C142.2, R120.1, R121.2
unnamed: C145.1, C146.1, C147.1, C148.1, DD1.AB6, DD1.AB8, DD1.AB10, FB11.1
unnamed: C149.1, C150.1, C151.1, C152.1, DD1.AA8, FB12.1
unnamed: C153.1, C154.1, C155.1, C156.1, C157.1, DD1.A24, DD1.AD24, DD1.G24, DD1.R24, DD1.W24, FB13.1
unnamed: C158.1, C159.1, J17.39, J17.40, J18.39, J18.40, R145.1
unnamed: D1.1, R99.1
unnamed: D1.2, R102.1
unnamed: D2.1, R103.1
unnamed: D2.2, R106.1
unnamed: DD1.A9, R123.1
unnamed: DD1.A10, R134.1
unnamed: DD1.A11, R140.1
unnamed: DD1.A12, R138.1
unnamed: DD1.AA5, R48.1
unnamed: DD1.B9, R124.1
unnamed: DD1.B10, R129.1
unnamed: DD1.B11, R139.1
unnamed: DD1.B12, R136.1
unnamed: DD1.C8, R125.1
unnamed: DD1.C9, R133.1
unnamed: DD1.C11, R135.1
unnamed: DD1.C13, R24.1
unnamed: DD1.C15, R89.2
unnamed: DD1.C19, R2.2
unnamed: DD1.D9, R128.1
unnamed: DD1.D11, R132.1
unnamed: DD1.D14, R92.2
unnamed: DD1.E10, R126.1
unnamed: DD1.E11, R127.1
unnamed: DD1.E12, R137.1
unnamed: DD1.E14, R91.2
unnamed: DD1.F2, R95.1
unnamed: DD1.F5, R96.1
unnamed: DD1.F11, R130.1
unnamed: DD1.F12, R131.1
unnamed: DD1.F13, R122.1
unnamed: DD1.F15, R90.2
unnamed: DD1.H1, R97.1
unnamed: DD1.H2, R98.1
unnamed: DD1.H6, R93.1
unnamed: DD1.J6, R94.1
unnamed: DD1.J17, R10.2
unnamed: DD1.K2, R112.2
unnamed: DD1.K3, R114.2
unnamed: DD1.K4, R115.2
unnamed: DD1.L6, R116.2
unnamed: DD1.M23, R11.2
unnamed: DD1.M24, R12.2
unnamed: DD1.N1, R75.1
unnamed: DD1.N2, R77.1
unnamed: DD1.N3, R79.1
unnamed: DD1.N4, R81.1
unnamed: DD1.N5, R83.1
unnamed: DD1.P1, R71.1
unnamed: DD1.P2, R67.1
unnamed: DD1.P5, R69.1
unnamed: DD1.P6, R63.1
unnamed: DD1.P7, R61.1
unnamed: DD1.R3, R73.1
unnamed: DD1.R4, R65.1
unnamed: DD1.T5, R78.2
unnamed: DD1.T6, R80.2
unnamed: DD1.U4, R68.2
unnamed: DD1.U5, R82.2
unnamed: DD1.V1, R84.2
unnamed: DD1.V2, R76.2
unnamed: DD1.V4, R72.2
unnamed: DD1.V5, R74.2
unnamed: DD1.V6, R70.2
unnamed: DD1.W1, R62.2
unnamed: DD1.W2, R64.2
unnamed: DD1.Y5, R66.2
unnamed: FB8.2, J13.5
unnamed: FB9.2, R118.2
unnamed: FB10.2, R119.2
unnamed: J1.SH1, J1.SH2
unnamed: J16.2, Q2.1, R141.2
unnamed: R17.1, U3.L8
unnamed: R18.1, U3.L9
unnamed: R22.1, U4.L8
unnamed: R23.1, U4.L9
unnamed: R41.2, U12.3
unnamed: R107.1, U13.3
unnamed: R117.2, U14.32
unnamed: R146.1, R147.1, U16.9
RTC_32kHz: R39.2, U11.1
RTC_nINT: R40.2, U11.3

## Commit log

2019-10-30 Commit...
2019-10-30 Work in progress...
2019-10-30 Work in progress... DDR3.sch
2019-10-31 Changes in DDR3.sch
2019-10-31 Added new schematic sheets.
2019-11-01 Added schematic sheet for DDR3 x16 chips; added submodule Libraries/KiCAD
2019-11-01 ULPI.sch: USB3300 ic
2019-11-01 ULPI.sch: ULPI complited...
2019-11-01 ULPI.sch: fix in ULPI ...
2019-11-01 Changes in TRACE.sch and SATA.sch
2019-11-05 Changes in TRACE, EJTAG, JTAG... Updated CPU symbol.
2019-11-05 Changes in TRACE...
2019-11-06 Renamed some sheets, added libs for PCIe/104 OneBank
2019-11-06 Added sheets AT24CS04.sch RTC_DS3231.sch TCA9406DC.sch
2019-11-06 Fix in I2C, added TXB0108PWR.sch
2019-11-06 Changes in CPU_GPIO.sch
2019-11-06 Added connector 2x40 in CPU_GPIO.sch
2019-11-07 Changes in CPU_BOOT.sch
2019-11-07 Changes in DDR3_chip.sch
2019-11-11 Changes in CPU_POWER
2019-11-11 Fix in VPVT_GPVT.sch
2019-11-14 Added capacitors to power lines in PCIE, DDR3, 10GEth.
2019-11-14 Changes in CPU_1GEth.sch
2019-11-19 Added resistors in ULPI, Added crystal 25MHz
2020-01-17 Working in CPU_SATA.sch, added SATA_CON.sch
2020-01-17 Working in CPU_SATA.sch
2020-01-27 Changes in CPU_SATA.sch
2020-01-29 Added symbol and schematic for SN74AVC4T774PWR logic level converter
2020-01-29 Changes in CPU_SPI.sch
2020-08-15 Added some footprints
